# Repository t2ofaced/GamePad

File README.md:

# GamePad

GamePad is a handheld gamepad built for the BBC microbit V2 the idea is really simple - plug and play, just plug the microbit into the GamePad through the edge connector of the gamepad and playy, the GamePad have 7 buttons and 4 of buttons are on left side for movement UP , LEFT, RIGHT, DOWN and 3 buttons on right Menu, A, and B it also includes a 1.8" colour TFT display, and a rechargeable 18650 battery with USB-C charging and protection, so it can be used without a cable.

<p align="center">
  <br>
  <em>Figure 1: GamePad Render</em>
</p>

## What is it

I wanted to make an offline gamepad for myself but never tried for some reason most DIY gamepads i saw most of the game consoles were built on an ESP or a raspberry pi and later i came across the microbit and thought why not make a gamepad for it it is inspired by the Game Boy Micro but the design and the function are a diffrent 

Most microbit gamepads don't have a display so i added one the idea is simple flash a game onto the microbit, plug it into the edge connector on the gamepad and play the microbit already has a speaker on it, so i didn't add a buzzer

<p align="center">
  <br>
  <em>Figure 2</em>
</p>

## Working

The microbit sits in an edge connector on the top side of the GamePad PCB

<p align="center">
  <br>
  <em>Figure 3</em>
</p>

This GamePad have

- **7 buttons:** 4 for direction (up, down, left, right) and 3 extra function buttons like menu or mute, their function changes from game to game like they are game dependent
- **Display:** a 1.8" ST7735 TFT display like obviously we need a display for gamepad also i couldn't find any footprint or 3D model for the display version i am using so all of my renders are without display
- **LEDs on the back:** controlled by a slider switch. The slider connects the board's 3V3 to the LED 3V3 line that powers all of them this is just for fun no functional use to be honest
- **Battery indicator:** a voltage divider reads the battery level and sends it to the microbit, which decides if the battery is low this also have Charging and charged indicators
- **Power slider:** decides whether BAT+ reaches the LDO no input to the LDO means no 3V3, and no 3V3 means no LEDs, no display and no microbit, so the whole board is off.

<p align="center">
  <br>
  <em>Figure 4</em>
</p>

## Schematics & Circuitry

This PCB was designed in KiCad, as it is free

<p align="center">
  <br>
  <em>Figure 5: Schematic</em>
</p>

I couldn't find a footprint for the display so i used a 1x08 male header for it

## Routing

<p align="center">
  <br>
  <em>Figure 6: Routing</em>
</p>

<p align="center">
  <br>
  <em>Figure 7: Routing</em>
</p>

I poured copper with the GND net on both the top and bottom layers, and added vias to connect the two layers i also added M3 holes for mounting

## 3D view

<p align="center">
  <br>
  <em>Figure 8: PCB with 3D models, exported as .step so I could design the case around it</em>
</p>

## Case / CAD

The Case/CAD is designed in Onshape

**Onshape:** [Open CAD model](https://cad.onshape.com/documents/08b3f6e79f648ac5b1a837d6/w/fd33090a4ac3aeb19b806cc8/e/8d36c46b3c2b914df7cd311f)
**Onshape:** [Assembly Link](https://cad.onshape.com/documents/08b3f6e79f648ac5b1a837d6/w/fd33090a4ac3aeb19b806cc8/e/730c3faaf1a0686c555cb4f5)

For the case i went with two transparent acrylic panels, one on top and one on bottom the PCB sits between them, held by hex spacers i also made button extenders which can be 3D printed.

<p align="center">
  <br>
  <em>Figure 9: Top plate</em>
</p>

<p align="center">
  <br>
  <em>Figure 10: Top plate</em>
</p>

<p align="center">
  <br>
  <em>Figure 11: Bottom plate</em>
</p>

<p align="center">
  <br>
  <em>Figure 12: Both panels together</em>
</p>

<p align="center">
  <br>
  <em>Figure 13: Final GamePad</em>
</p>

## Bill of Materials

| Part Name | Quantity | Link | Info | Price (USD) |
|-----------|:--------:|------|------|------------:|
| JLCPCB PCB Manufacturing & Shipping | 5 | [Link](https://jlcpcb.com/) | PCB | $17.75 |
| Micro:bit Edge Connector 40-pin 90 Degree | 1 | [Link](https://www.flipkart.com/yellow-tommy-microbit-40-pin-header-90-degree-angle-edge-connector-pack-5-electronic-components-hobby-kit/p/itm9f87dd64a093b) | Microbit Edge Connector | $7.43 |
| BBC Microbit V2 | 1 | [Link](https://robu.in/product/bbc-micro-bit-v2-pocket-sized-single-board-computer/) | MCU | $22.85 |
| 18650 SMD Single Battery Holder | 1 | [Link](https://robu.in/product/18650-battery-holder-smd-smt/) | 18650 Battery Holder | $0.5 |
| 18650 Battery| 1 | [Link](https://robu.in/product/dmegc-inr18650-26e-3-7v-2600mah-li-ion-battery/) | 18650 Battery | $2.44 |
| TP4056 SMD IC | 1 | [Link](https://robu.in/product/1-month-warranty-1253/) | Li-ion Charger IC | $0.1 |
| DW01A Battery Protection IC SOT-23-6 | 3 | [Link](https://robu.in/product/dw01a-4-3v-lithium-ion-lithium-polymer-battery-protection-ic-6pin-sot-23/) | Battery Protection IC | $0.13 |
| FS8205A Dual MOSFET SOT-23-6 | 2 | [Link](https://robu.in/product/1-month-warranty-398/) | Dual N-MOSFET | $0.18 |
| SPX3819M5-L-3.3 LDO SOT-23-5 | 1 | [Link](https://robu.in/product/spx3819m5-l-3-3-tr-500ma-low-noise-ldo-voltage-regulator-5-pin-sot-23/) | 3.3V LDO Regulator | $0.24 |
| AO3400A MOSFET SOT-23 | 1 | [Link](https://robu.in/product/1-month-warranty-414/) | N-MOSFET | $0.11 |
| SMF30A TVS Diode SOD-123FL | 10 | [Link](https://robu.in/product/smf30a-slkor-4-1a-48-4v-33-3v-30v-sod-123fl-esd-and-surge-protection-tvs-esd-rohs/) | TVS Diode | $0.1 |
| USB Type-C 16-Pin Female SMD | 1 | [Link](https://robu.in/product/type-c-31-m-16-hroparts-1-6p-female-type-c-smd-usb/) | USB-C Port | $0.4 |
| 1.8 inch SPI TFT 128x160 ST7735 Display | 1 | [Link](https://robu.in/product/62060/) | TFT Display | $3.29 |
| Tactile Push Button 6x6x4.3mm | 7 | [Link](https://robu.in/product/6x6x8mm-tactile-push-button-switch-pack-of-20/) | Tactile Switches | $0.15 |
| Slide Switch 3-Pin SPDT 2.54mm | 7 | [Link](https://robu.in/product/1-month-warranty-255/) | SPDT Slide Switch | $0.13 |
| 0805 SMD LED | 7 | [Link](https://robu.in/product/0805-surface-mount-led-green-50-pcs/) | SMD LED | $0.1 |
| 100nF 0805 SMD Capacitor | 14 | [Link](https://robu.in/product/100nf-0805-surface-mount-multilayer-ceramic-capacitor-pack-of-40/) | 100nF Capacitor | $0.13 |
| 10uF 0805 SMD Capacitor | 6 | [Link](https://robu.in/product/10uf-10000nf-25-v-capacitor-0805-smd-package-pack-of-10/) | 10uF Capacitor | $0.20 |
| 100 Ohm 0805 Resistor | 1 | [Link](https://robu.in/product/100-ohm-1-4w-0805-surface-mount-chip-resistor-10-pcs/) | Resistor | $0.11 |
| 470 Ohm 0805 Resistor | 5 | [Link](https://robu.in/product/rc0805jr-07470kl-yageo-smd-chip-resistor-470-kohm-%C2%B1-5-125-mw-0805-2012-metric-thick-film-general-purpose/) | Resistor | $0.1 |
| 1K 0805 Resistor | 4 | [Link](https://robu.in/product/1k-ohm-1-4w-0805-surface-mount-chip-resistor-pack-of-10/) | Resistor | $0.1 |
| 1.2K 0805 Resistor | 1 | [Link](https://robu.in/product/rc0805fr-071k2l-yageo-smd-chip-resistor-1-2-kohm-%C2%B1-1-125-mw-0805-2012-metric-thick-film-general-purpose/) | Resistor | $0.1 |
| 5.1K 0805 Resistor | 2 | [Link](https://robu.in/product/ac0805fr-075k1l-yageo-res-thick-film-0805-5-1k-ohm-1-0-125w1-8w-%C2%B1100ppm-c-pad-smd-t-r-automotive-aec-q200/) | Resistor | $0.1 |
| 10K 0805 Resistor | 2 | [Link](https://robu.in/product/rc0805jr-0710kl-yageo-res-thick-film-0805-10k-ohm-5-0-125w1-8w-%C2%B1100ppm-c-pad-smd-t-r/) | Resistor | $0.1 |
| 120K 0805 Resistor | 1 | [Link](https://robu.in/product/rc0805fr-07120kl-yageo-res-thick-film-0805-120k-ohm-1-0-125w1-8w-%C2%B1100ppm-c-pad-smd-t-r/) | Resistor | $0.1 |
| 300K 0805 Resistor | 1 | [Link](https://robu.in/product/rc0805fr-07300kl-yageo-res-thick-film-0805-300k-ohm-1-0-125w1-8w-%25c2%25b1100ppm-c-pad-smd-t-r/) | Resistor | $0.1 |
| **TOTAL** | | | |  $64.21 |

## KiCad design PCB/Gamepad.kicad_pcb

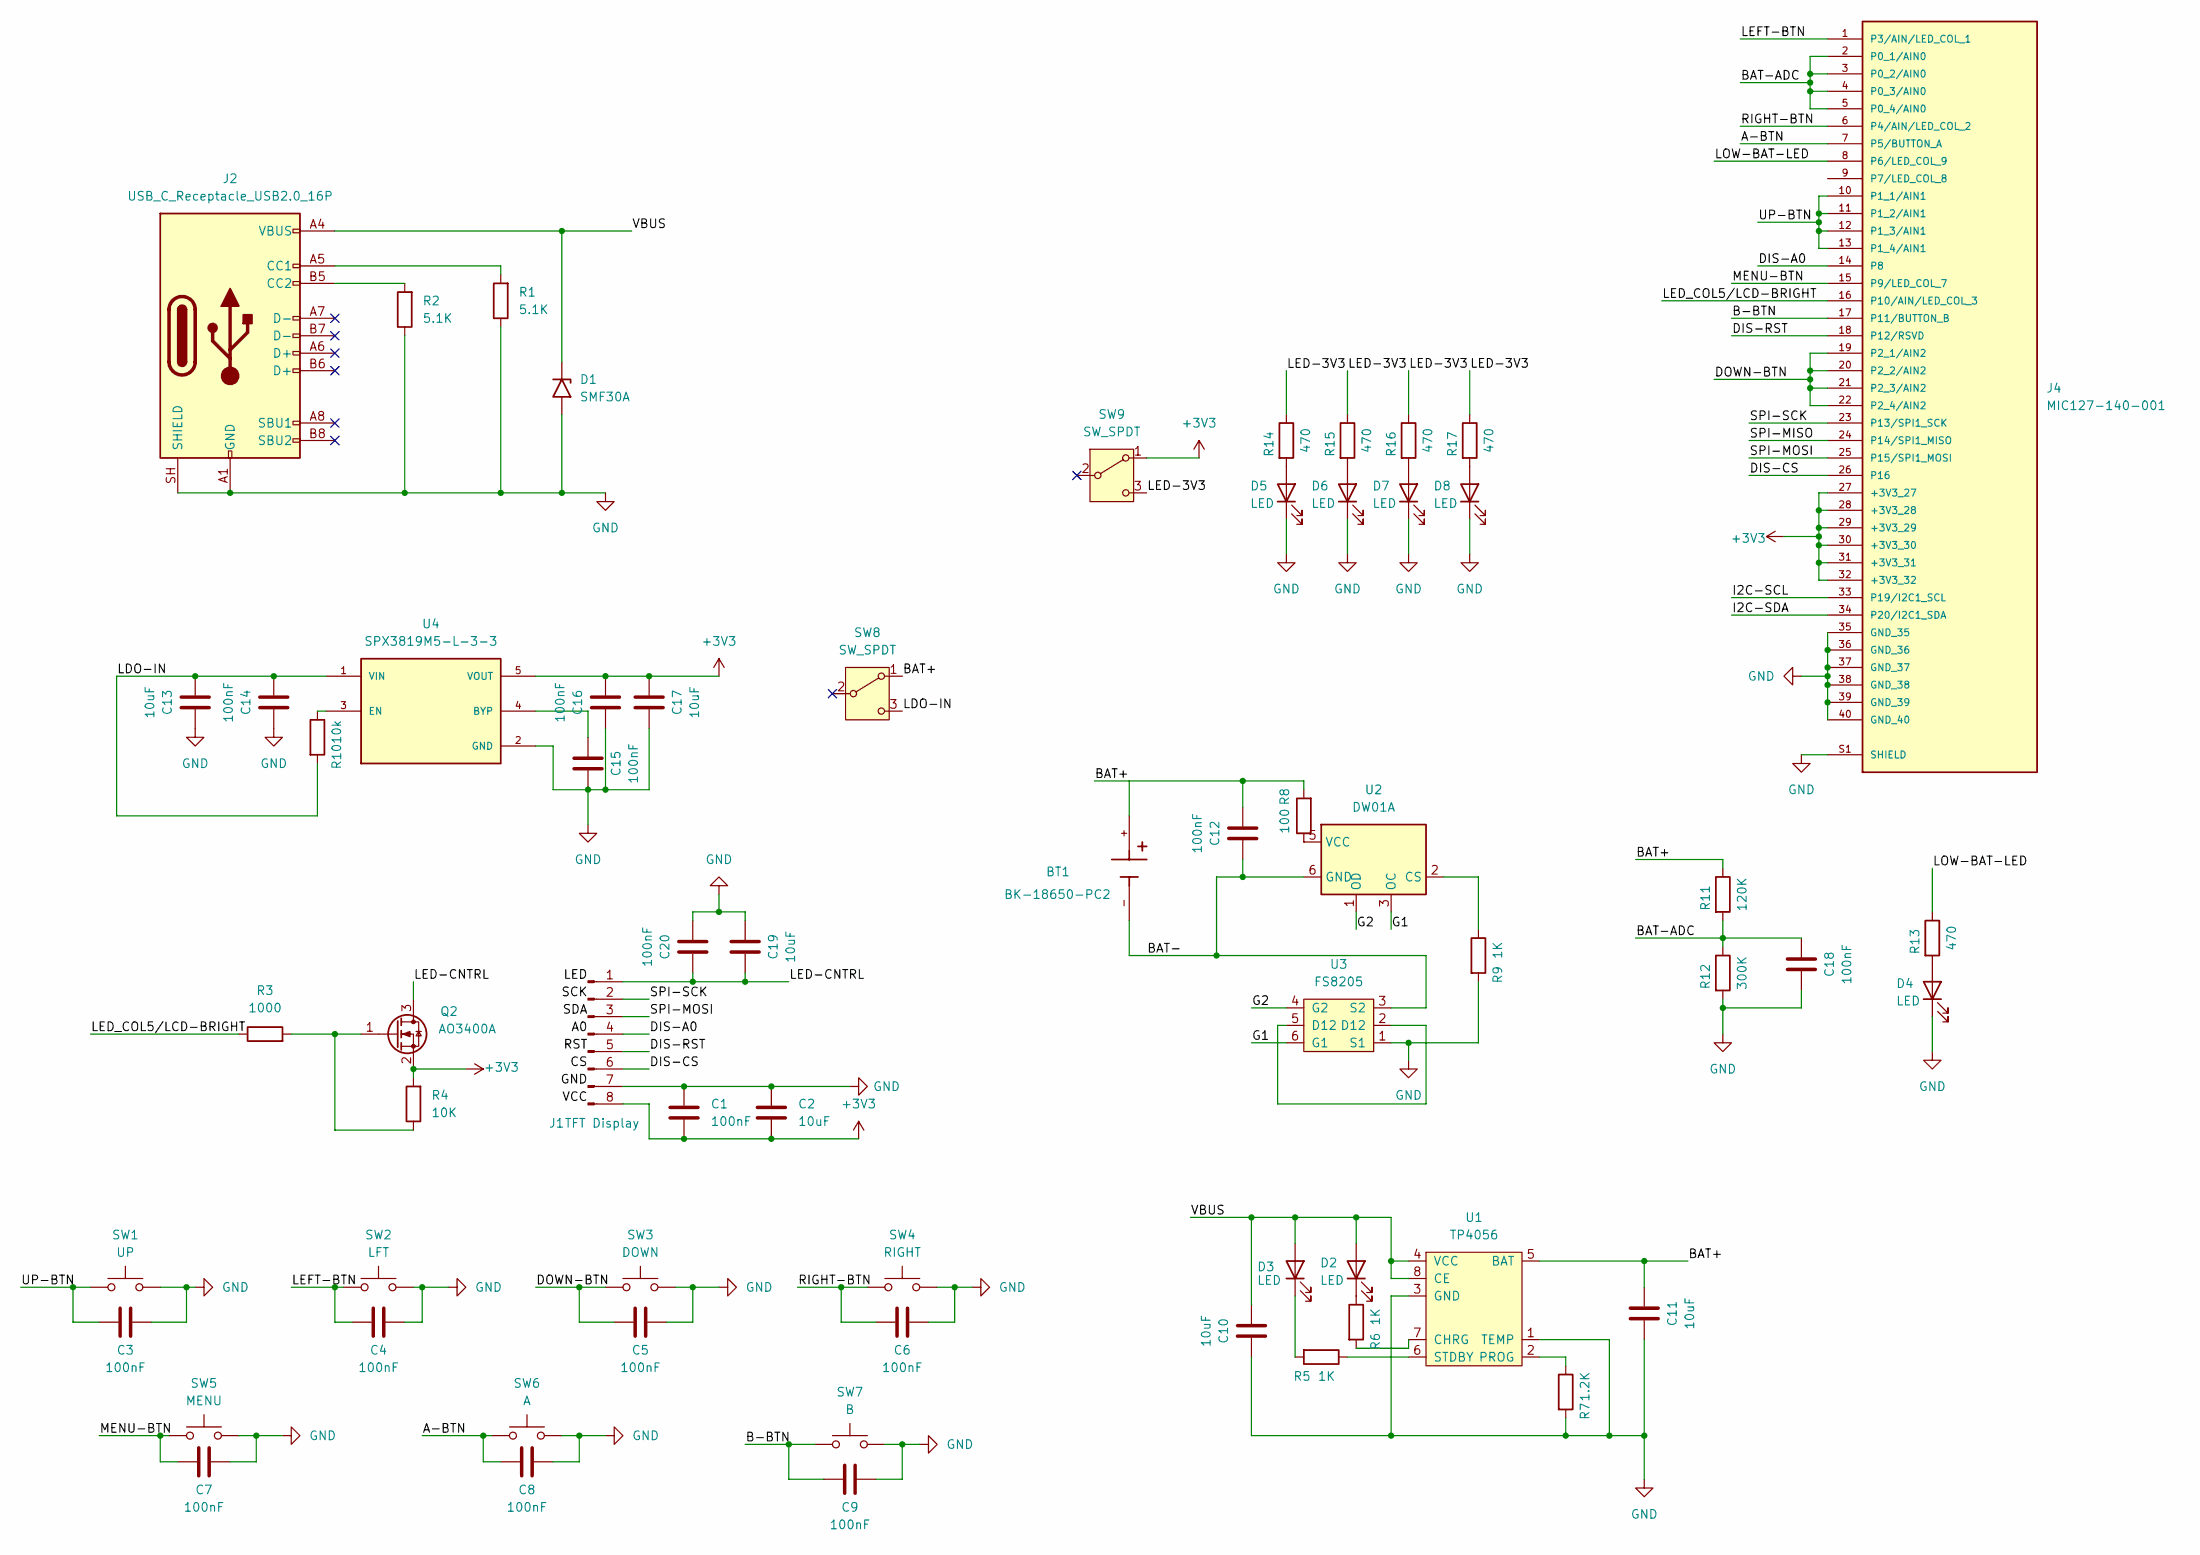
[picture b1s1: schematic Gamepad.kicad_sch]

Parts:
BT1: BK-18650-PC2; Keystone_1042_1x18650; PARTREV F
C1, C3, C4, C5, C6, C7, C8, C9, C12, C14, C15, C16, C18, C20: 100nF; C_0805_2012Metric
C2, C10, C11, C13, C17, C19: 10uF; C_0805_2012Metric
D1: SMF30A; D_SMF
D2, D3, D4, D5, D6, D7, D8: LED; LED_0805_2012Metric
J1: TFT Display; PinHeader_1x08_P2.54mm_Vertical
J2: USB_C_Receptacle_USB2.0_16P; USB_C_Receptacle_HCTL_HC-TYPE-C-16P-01A
J4: MIC127-140-001; DONGGUAN_MIC127-140-001; PARTREV A
Q2: AO3400A; SOT-23
R1, R2: 5.1K; R_0805_2012Metric
R3: 1000; R_0805_2012Metric
R4: 10K; R_0805_2012Metric
R5, R6, R9: 1K; R_0805_2012Metric
R7: 1.2K; R_0805_2012Metric
R8: 100; R_0805_2012Metric
R10: 10k; R_0805_2012Metric
R11: 120K; R_0805_2012Metric
R12: 300K; R_0805_2012Metric
R13, R14, R15, R16, R17: 470; R_0805_2012Metric
SW1: UP; SW_PUSH_6mm_H4.3mm
SW2: LFT; SW_PUSH_6mm_H4.3mm
SW3: DOWN; SW_PUSH_6mm_H4.3mm
SW4: RIGHT; SW_PUSH_6mm_H4.3mm
SW5: MENU; SW_PUSH_6mm_H4.3mm
SW6: A; SW_PUSH_6mm_H4.3mm
SW7: B; SW_PUSH_6mm_H4.3mm
SW8, SW9: SW_SPDT; SW_Slide-03_Wuerth-WS-SLTV_10x2.5x6.4_P2.54mm
U1: TP4056; SOP-8-1EP_4.57x4.57mm_P1.27mm_EP4.57x4.45mm; LCSC C16581
U2: DW01A; SOT-23-6
U3: FS8205; SOT-23-6; LCSC C32254
U4: SPX3819M5-L-3-3; SOT95P280X145-5N; PARTREV 2.0.5

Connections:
+3V3: C1.2, C2.2, C16.2, C17.1, J1.8, J4.27 (+3V3_27), J4.28 (+3V3_28), J4.29 (+3V3_29), J4.30 (+3V3_30), J4.31 (+3V3_31), J4.32 (+3V3_32), Q2.2 (S), R4.2, SW9.1 (A), U4.5 (VOUT)
/A-BTN: C8.2, J4.7 (P5/BUTTON_A), SW6.1
/B-BTN: C9.2, J4.17 (P11/BUTTON_B), SW7.1
/BAT+: BT1.1, C11.1, C12.2, R8.2, R11.1, SW8.1 (A), U1.5 (BAT)
/BAT-: BT1.2, BT1.-, C12.1, U2.6 (GND), U3.3 (S2)
/BAT-ADC: C18.1, J4.2 (P0_1/AIN0), J4.3 (P0_2/AIN0), J4.4 (P0_3/AIN0), J4.5 (P0_4/AIN0), R11.2, R12.1
/DIS-A0: J1.4, J4.14 (P8)
/DIS-CS: J1.6, J4.26 (P16)
/DIS-RST: J1.5, J4.18 (P12/RSVD)
/DOWN-BTN: C5.2, J4.19 (P2_1/AIN2), J4.20 (P2_2/AIN2), J4.21 (P2_3/AIN2), J4.22 (P2_4/AIN2), SW3.1
/G1: U2.3 (OC), U3.6 (G1)
/G2: U2.1 (OD), U3.4 (G2)
/I2C-SCL: J4.33 (P19/I2C1_SCL)
/I2C-SDA: J4.34 (P20/I2C1_SDA)
/LDO-IN: C13.2, C14.2, R10.2, SW8.3 (C), U4.1 (VIN)
/LED-3V3: R14.1, R15.1, R16.1, R17.1, SW9.3 (C)
/LED-CNTRL: C19.2, C20.1, J1.1, Q2.3 (D)
/LED_COL5/LCD-BRIGHT: J4.16 (P10/AIN/LED_COL_3), R3.1
/LEFT-BTN: C4.2, J4.1 (P3/AIN/LED_COL_1), SW2.1
/LOW-BAT-LED: J4.8 (P6/LED_COL_9), R13.1
/MENU-BTN: C7.2, J4.15 (P9/LED_COL_7), SW5.1
/RIGHT-BTN: C6.2, J4.6 (P4/AIN/LED_COL_2), SW4.1
/SPI-MISO: J4.24 (P14/SPI1_MISO)
/SPI-MOSI: J1.3, J4.25 (P15/SPI1_MOSI)
/SPI-SCK: J1.2, J4.23 (P13/SPI1_SCK)
/UP-BTN: C3.2, J4.10 (P1_1/AIN1), J4.11 (P1_2/AIN1), J4.12 (P1_3/AIN1), J4.13 (P1_4/AIN1), SW1.1
/VBUS: C10.2, D1.1 (A1), D2.2 (A), D3.2 (A), J2.A4 (VBUS), J2.A9 (VBUS), J2.B4 (VBUS), J2.B9 (VBUS), U1.4 (VCC), U1.8 (CE)
GND: C1.1, C2.1, C3.1, C4.1, C5.1, C6.1, C7.1, C8.1, C9.1, C10.1, C11.2, C13.1, C14.1, C15.2, C16.1, C17.2, C18.2, C19.1, C20.2, D1.2 (A2), D4.1 (K), D5.1 (K), D6.1 (K), D7.1 (K), D8.1 (K), J1.7, J2.A1 (GND), J2.A12 (GND), J2.B1 (GND), J2.B12 (GND), J2.SH (SHIELD), J4.35 (GND_35), J4.36 (GND_36), J4.37 (GND_37), J4.38 (GND_38), J4.39 (GND_39), J4.40 (GND_40), J4.S1 (SHIELD), J4.S2 (SHIELD), R1.1, R2.1, R7.2, R9.2, R12.2, SW1.2, SW2.2, SW3.2, SW4.2, SW5.2, SW6.2, SW7.2, U1.1 (TEMP), U1.3 (GND), U3.1 (S1), U4.2 (GND)
unnamed: D2.1 (K), R6.1
unnamed: D3.1 (K), R5.2
unnamed: D4.2 (A), R13.2
unnamed: D5.2 (A), R14.2
unnamed: D6.2 (A), R15.2
unnamed: D7.2 (A), R16.2
unnamed: D8.2 (A), R17.2
unnamed: J2.A5 (CC1), R1.2
unnamed: J2.B5 (CC2), R2.2
unnamed: Q2.1 (G), R3.2, R4.1
unnamed: R6.2, U1.7 (CHRG)
unnamed: R7.1, U1.2 (PROG)
unnamed: R5.1, U1.6 (STDBY)
unnamed: R9.1, U2.2 (CS)
unnamed: R8.1, U2.5 (VCC)
unnamed: U3.2 (D12), U3.5 (D12)
unnamed: C15.1, U4.4 (BYP)
unnamed: R10.1, U4.3 (EN)

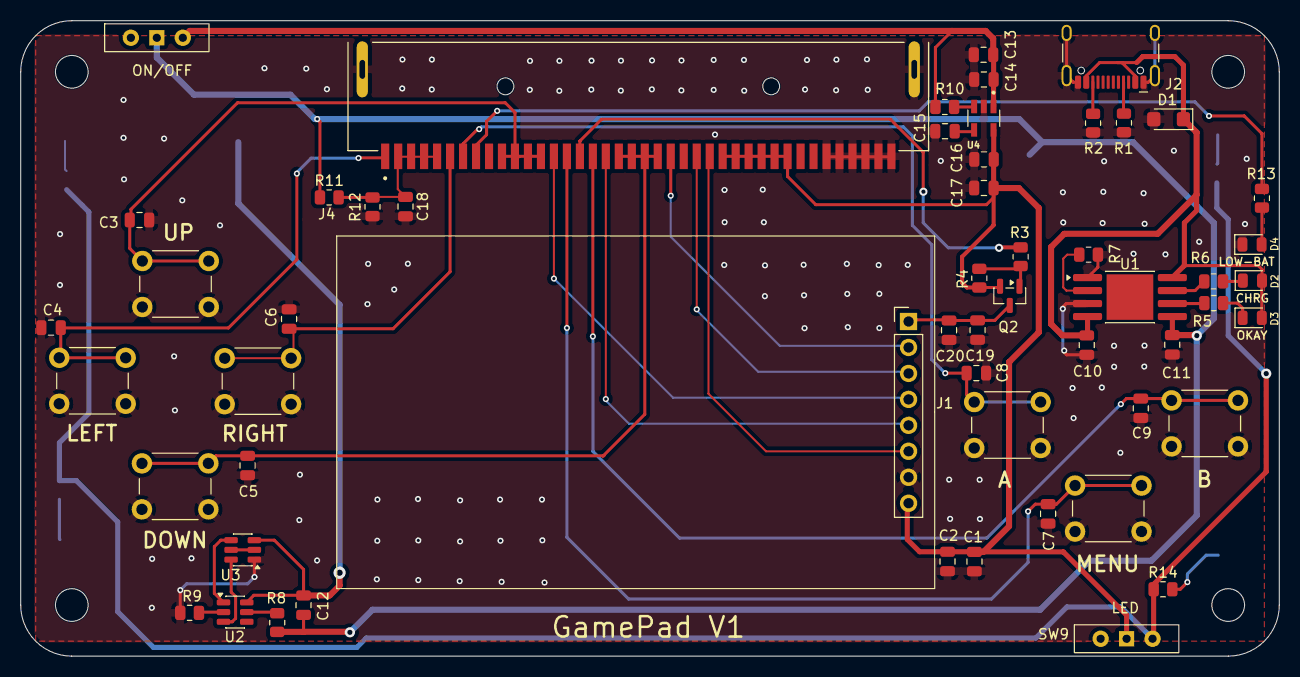
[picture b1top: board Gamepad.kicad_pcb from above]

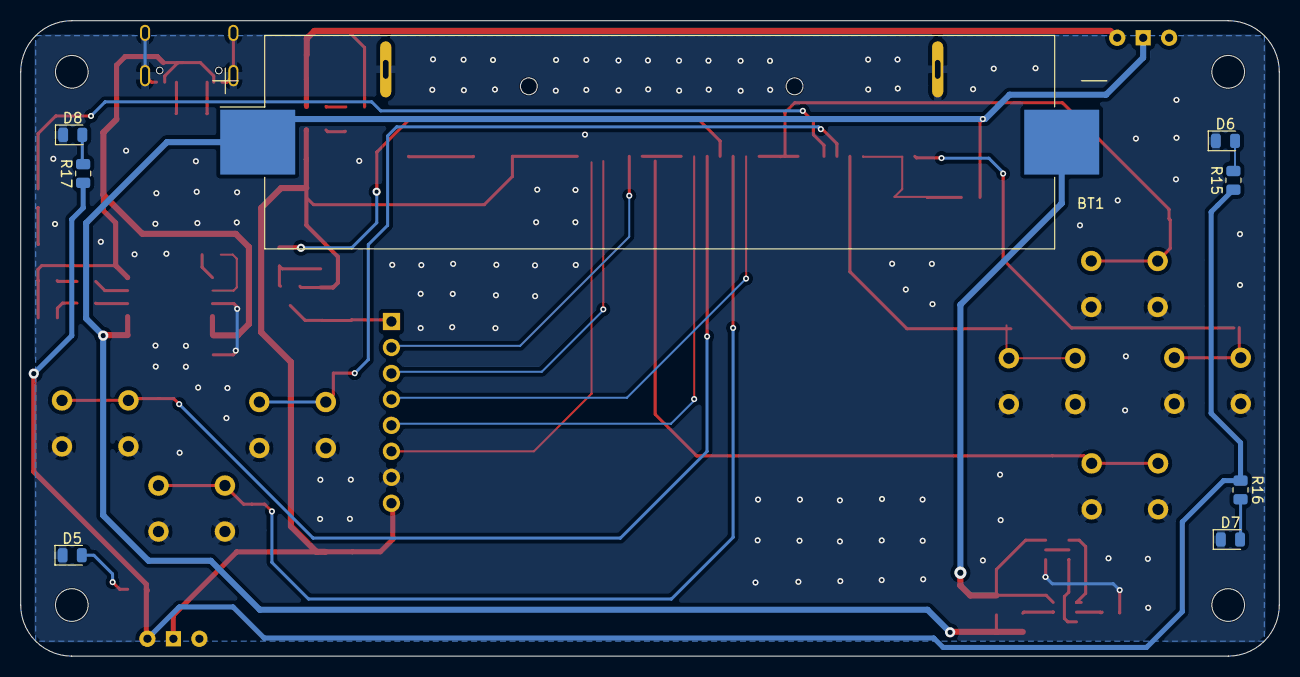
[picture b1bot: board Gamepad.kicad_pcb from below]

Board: 2 copper layers, 123.1 x 62.2 mm, 63 parts (8 on the bottom side), 43 nets.

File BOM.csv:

Part Name,Quantity,Link,Info,Price (USD)
JLCPCB PCB Manufacturing & Shipping,5,https://jlcpcb.com/,PCB,$17.75
Micro:bit Edge Connector 40-pin 90 Degree,1,https://www.flipkart.com/yellow-tommy-microbit-40-pin-header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,Microbit Edge Connector,$7.43
BBC Microbit V2,1,https://robu.in/product/bbc-micro-bit-v2-pocket-sized-single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,MCU,$22.85
18650 SMD Single Battery Holder,1,https://robu.in/product/18650-battery-holder-smd-smt/,18650 Battery Holder,$.5
TP4056 SMD IC,1,https://robu.in/product/1-month-warranty-1253/,Li-ion Charger IC,$.1
DW01A Battery Protection IC SOT-23-6,3,https://robu.in/product/dw01a-4-3v-lithium-ion-lithium-polym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,Battery Protection IC,$.13
FS8205A Dual MOSFET SOT-23-6,2,https://robu.in/product/1-month-warranty-398/,Dual N-MOSFET,$.18
SPX3819M5-L-3.3 LDO SOT-23-5,1,https://robu.in/product/spx3819m5-l-3-3-tr-500ma-low-noise-l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,3.3V LDO Regulator,$.24
AO3400A MOSFET SOT-23,1,https://robu.in/product/1-month-warranty-414/,N-MOSFET,$.11
SMF30A TVS Diode SOD-123FL,10,https://robu.in/product/smf30a-slkor-4-1a-48-4v-33-3v-30v-so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,TVS Diode,$0.1
USB Type-C 16-Pin Female SMD,1,https://robu.in/product/type-c-31-m-16-hroparts-1-6p-female-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,USB-C Port,$0.4
1.8 inch SPI TFT 128x160 ST7735 Display,1,https://robu.in/product/62060/,TFT Display,$3.29
Tactile Push Button 6x6x4.3mm,7,https://robu.in/product/6x6x8mm-tactile-push-button-switch-p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,Tactile Switches,$0.15
Slide Switch 3-Pin SPDT 2.54mm,7,https://robu.in/product/1-month-warranty-255/,SPDT Slide Switch,$0.13
0805 SMD LED,7,https://robu.in/product/0805-surface-mount-led-green-50-pcs/,SMD LED,$0.1
100nF 0805 SMD Capacitor,14,https://robu.in/product/100nf-0805-surface-mount-multilayer-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,100nF Capacitor,$0.13
10uF 0805 SMD Capacitor,6,https://robu.in/product/10uf-10000nf-25-v-capacitor-0805-smd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,10uF Capacitor,$0.20
100 Ohm 0805 Resistor,1,https://robu.in/product/100-ohm-1-4w-0805-surface-mount-chip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,Resistor,$0.11
470 Ohm 0805 Resistor,5,https://robu.in/product/rc0805jr-07470kl-yageo-smd-chip-resi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,Resistor,$0.1
1K 0805 Resistor,4,https://robu.in/product/1k-ohm-1-4w-0805-surface-mount-chip-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,Resistor,$0.1
1.2K 0805 Resistor,1,https://robu.in/product/rc0805fr-071k2l-yageo-smd-chip-resis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,Resistor,$0.1
5.1K 0805 Resistor,2,https://robu.in/product/ac0805fr-075k1l-yageo-res-thick-film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,Resistor,$0.1
10K 0805 Resistor,2,https://robu.in/product/rc0805jr-0710kl-yageo-res-thick-film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,Resistor,$0.1
120K 0805 Resistor,1,https://robu.in/product/rc0805fr-07120kl-yageo-res-thick-fil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,Resistor,$0.1
300K 0805 Resistor,1,https://robu.in/product/rc0805fr-07300kl-yageo-res-thick-fil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,Resistor,$0.1
TOTAL, , , ,~ $61.81
